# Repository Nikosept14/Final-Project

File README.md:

# 🤖 Humanoid Dancing Robot – 29 DOF Controller

This repository contains the source code and documentation for my undergraduate thesis:  
**"Rancang Bangun Sistem Kontroler 29-DOF pada Robot Penari Humanoid untuk Gerakan Tari yang Dinamis"**

---

## 📌 Project Description
This project focuses on the design and implementation of a **29 Degrees of Freedom (DOF) humanoid dancing robot**.  
The system utilizes an **ESP32 microcontroller** and **Dynamixel servomotors** to perform **dynamic dance movements**, following the guidelines of the **Indonesian Robot Contest (KRI) 2024**.  

The controller system is capable of:
- Coordinating **multi-DOF motion** for humanoid dance movements.
- Achieving flexibility and balance
- Executing pre-programmed dynamic dance sequences.

---

## 🛠️ Tech Stack
- **Hardware**: ESP32, Dynamixel Servomotors  
- **Software/Frameworks**: Arduino IDE / PlatformIO, C/C++  
- **Control Algorithm**: Multi-DOF Motion Control  
- **Reference**: KRI 2024 Dance Robot Guidelines

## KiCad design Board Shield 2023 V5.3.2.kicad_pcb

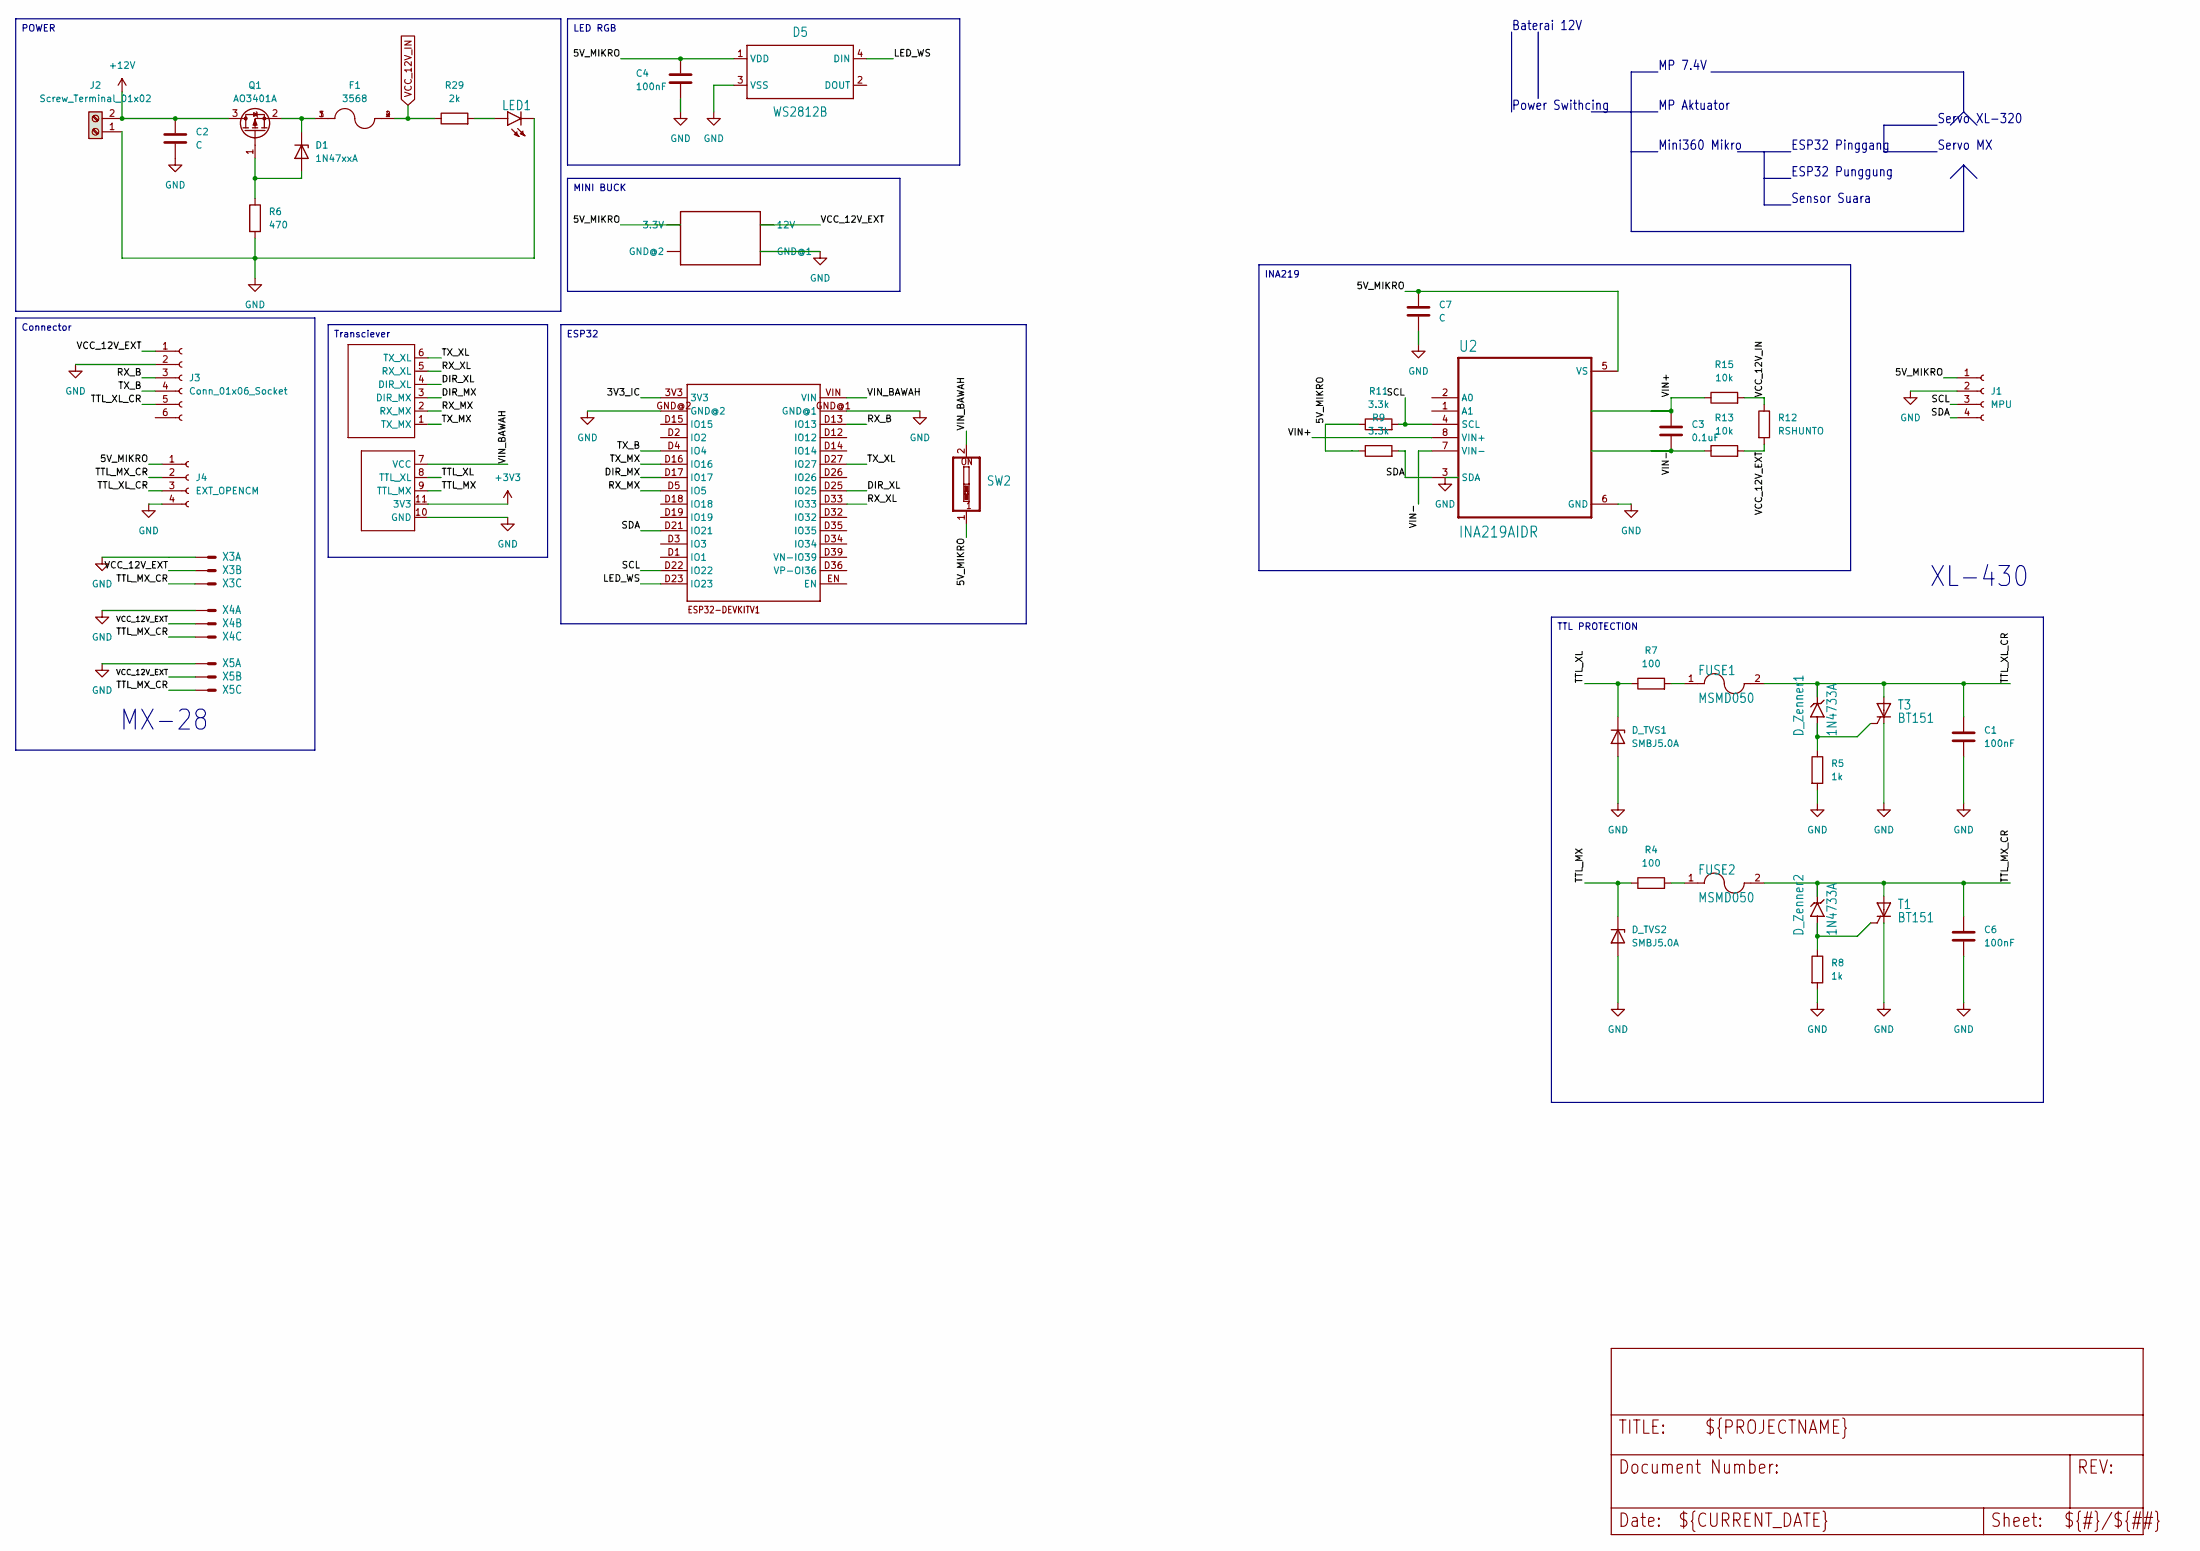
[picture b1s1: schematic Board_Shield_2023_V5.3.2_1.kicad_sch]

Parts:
C1, C4, C6: 100nF; C_0805_2012Metric
C2: C; CP_Elec_10x12.6
C3: 0.1uF; C_0805_2012Metric
C7: C; C_0805_2012Metric
D1: 1N47xxA; D_DO-41_SOD81_P7.62mm_Horizontal
D5: WS2812B; WS2812B_22900745
D_TVS1, D_TVS2: SMBJ5.0A; D_SMB
D_Zenner1, D_Zenner2: 1N4733A; D_DO-41_SOD81_P7.62mm_Horizontal
F1: 3568; FUSE_3568; PARTREV C
FUSE1, FUSE2: MSMD050; Fuse_1812_4532Metric
J1: MPU; 22-23-2041_165
J2: Screw_Terminal_01x02; TerminalBlock_MetzConnect_Type101_RT01602HBWC_1x02_P5.08mm_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
J3: Conn_01x06_Socket; 22-23-2061_165
J4: EXT_OPENCM; 22-23-2041_165
LED1: LEDCHIPLED_1206; CHIPLED_1206
MINI360: MP2307-MINI-360
Q1: AO3401A; SOT-23
R4, R7: 100; R_0805_2012Metric
R5, R8: 1k; R_0805_2012Metric
R6: 470; R_0805_2012Metric
R9, R11: 3.3k; R_0805_2012Metric
R12: RSHUNTO; R2512_334
R13, R15: 10k; R_0805_2012Metric
R29: 2k; R_0805_2012Metric
SW2: EDG-01_367
T1, T3: BT151; TO220CL
U2: INA219AIDR; SOIC127P599X175-8N
U$5: ESP32DEVKITV1; ESP32-DEVKITV1
U$6: TRANSCEIVER_2.0
X3, X4, X5: 22-23-2031

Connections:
+3V3: U$6.11 (3V3)
+12V: C2.1, J2.2, Q1.3 (D)
/Board Shield 2023 V5.3.2_1/3V3_IC: U$5.3V3
/Board Shield 2023 V5.3.2_1/5V_MIKRO: C4.1, C7.1, D5.1 (VDD), J1.1, J4.1, MINI360.V+OUT (3.3V), R9.1, R11.1, SW2.1, U2.5 (VS)
/Board Shield 2023 V5.3.2_1/DIR_MX: U$5.D17 (IO17), U$6.3 (DIR_MX)
/Board Shield 2023 V5.3.2_1/DIR_XL: U$5.D25 (IO25), U$6.4 (DIR_XL)
/Board Shield 2023 V5.3.2_1/LED_WS: D5.4 (DIN), U$5.D23 (IO23)
/Board Shield 2023 V5.3.2_1/RX_B: J3.3, U$5.D13 (IO13)
/Board Shield 2023 V5.3.2_1/RX_MX: U$5.D5 (IO5), U$6.2 (RX_MX)
/Board Shield 2023 V5.3.2_1/RX_XL: U$5.D33 (IO33), U$6.5 (RX_XL)
/Board Shield 2023 V5.3.2_1/SCL: J1.3, R11.2, U2.4 (SCL), U$5.D22 (IO22)
/Board Shield 2023 V5.3.2_1/SDA: J1.4, R9.2, U2.3 (SDA), U$5.D21 (IO21)
/Board Shield 2023 V5.3.2_1/TTL_MX: D_TVS2.1 (K), R4.1, U$6.9 (TTL_MX)
/Board Shield 2023 V5.3.2_1/TTL_MX_CR: C6.1, D_Zenner2.1 (K), FUSE2.2, J4.2, T1.A, X3.3 (S), X4.3 (S), X5.3 (S)
/Board Shield 2023 V5.3.2_1/TTL_XL: D_TVS1.1 (K), R7.1, U$6.8 (TTL_XL)
/Board Shield 2023 V5.3.2_1/TTL_XL_CR: C1.1, D_Zenner1.1 (K), FUSE1.2, J3.5, J4.3, T3.A
/Board Shield 2023 V5.3.2_1/TX_B: J3.4, U$5.D4 (IO4)
/Board Shield 2023 V5.3.2_1/TX_MX: U$5.D16 (IO16), U$6.1 (TX_MX)
/Board Shield 2023 V5.3.2_1/TX_XL: U$5.D27 (IO27), U$6.6 (TX_XL)
/Board Shield 2023 V5.3.2_1/VCC_12V_EXT: J3.1, MINI360.V+IN (12V), R12.2, R13.2, X3.2 (S), X4.2 (S), X5.2 (S)
/Board Shield 2023 V5.3.2_1/VIN+: C3.1, R15.1, U2.8 (VIN+)
/Board Shield 2023 V5.3.2_1/VIN-: C3.2, R13.1, U2.7 (VIN-)
/Board Shield 2023 V5.3.2_1/VIN_BAWAH: SW2.2, U$5.VIN, U$6.7 (VCC)
GND: C1.2, C2.2, C4.2, C6.2, C7.2, D5.3 (VSS), D_TVS1.2 (A), D_TVS2.2 (A), J1.2, J2.1, J3.2, J4.4, LED1.C, MINI360.GND_IN (GND@1), R5.2, R6.2, R8.2, T1.C, T3.C, U2.6 (GND), U$5.GND@1, U$5.GND@2, U$6.10 (GND), X3.1 (S), X4.1 (S), X5.1 (S)
unnamed: D1.2 (A), Q1.1 (G), R6.1
unnamed: D1.1 (K), F1.1, F1.3, Q1.2 (S)
unnamed: D_Zenner1.2 (A), R5.1, T3.G
unnamed: D_Zenner2.2 (A), R8.1, T1.G
unnamed: FUSE1.1, R7.2
unnamed: FUSE2.1, R4.2
unnamed: LED1.A, R29.2
VCC_12V_IN: F1.2, F1.4, R12.1, R15.2, R29.1

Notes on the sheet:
ESP32
INA219
MINI BUCK
Connector
TTL PROTECTION
POWER
Transciever
LED RGB
MX-28
Servo MX
Sensor Suara
Mini360 Mikro
ESP32 Pinggang
MP Aktuator
Baterai 12V
Power Swithcing
ESP32 Punggung
XL-430
MP 7.4V
Servo XL-320

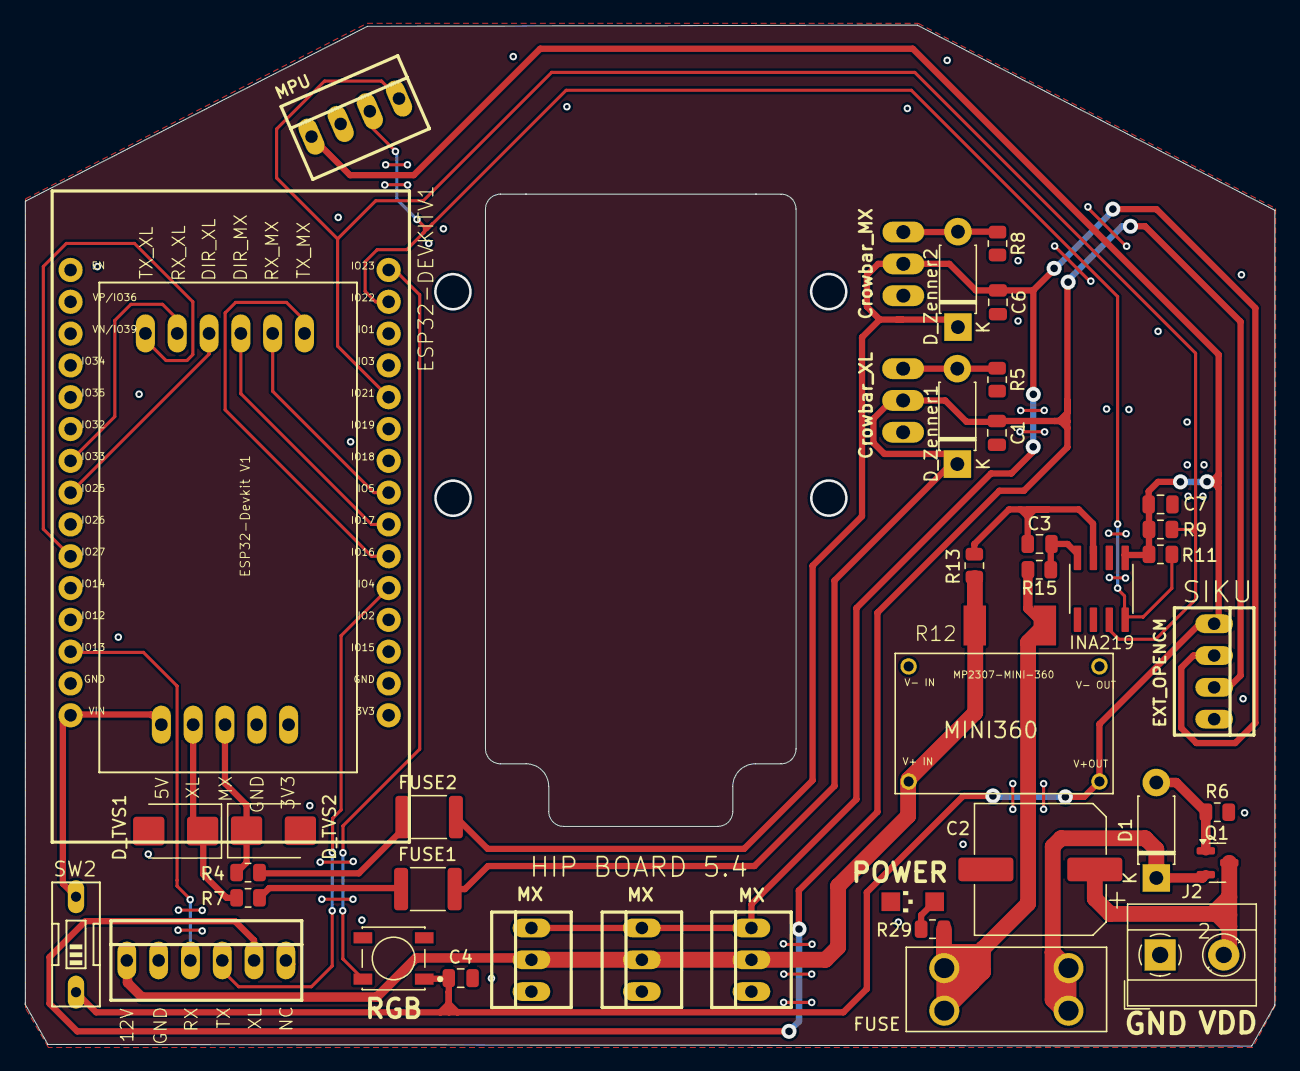
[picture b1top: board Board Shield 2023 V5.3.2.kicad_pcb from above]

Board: 2 copper layers, 99.8 x 81.5 mm, 42 parts (0 on the bottom side), 30 nets.

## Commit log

2025-08-20 README.md
